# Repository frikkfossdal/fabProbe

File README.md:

# Fab Touchprobe 

## What is it

A fabrication friendly design of a 3-DOF touch probe. At the heart of the design is a circuit board that lights up leds on probe contact. Probe is designed to be attached on [Jake Read's hotplate system](https://clank.tools/build/hotplate/index.html). 

## How to use it

The probe acts as a digital switch. Connect it to your favorite machine controller and start probing. 

**NB! First batch of circuits has wrong labeling on connector input. Ground and input voltage is switched. Study circuit before connecting and chech yourself!**

## How to make it

The repo contains all the files that are necassary to print the parts and make the circuit. There are currently two circuit designs: one that is pcb mill friendly (not tested!) and one circuit design meant for fabrication houses. I'm using the latter. Some notes: 

- Originally the probe uses [threaded steel-balls]() and dowels to form the kinematic mount but this could be modified to only use screws and dowels for easier sourcing.
- I print the probe casing with two different filaments, one transparent for making the circuit leds visible and one solid gray. If you rather print the casing as one solid merge the two casing bodies. 
- If you want to use a different probing stylus change the "nut diameter" of the nut on the *probe base* (see fusion model) to fit your chosen diameter. 

## BOM

| **Part Name**       | **Description**                   | **Quantity** | **Link**                                                                                  |
|---------------------|-----------------------------------|--------------|-------------------------------------------------------------------------------------------|
| threaded steel ball | typically found in delta printers | 6            | [amazon](https://www.amazon.com/Bolsen-Threaded-Kossel-3D-Printer-Magnetic/dp/B07HQ72H1R) |
| steel dowels 5x10mm |                                   | 3            | [mcmaster](https://www.mcmaster.com/93600a511/)                                           |
| probe stylus m3x50  |                                   | 1            | [ebay](https://www.ebay.com/itm/132811711640)                                             |
| m4button x 8mm      |                                   | 6            | [mcmaster](https://www.mcmaster.com/93600a511/)                                           |
| m3button x 14mm     |                                   | 3            | [mcmaster](https://www.mcmaster.com/92095A168/)                                           |
| m3_locknut          |                                   | 3            | [mcmaster](https://www.mcmaster.com/90576A102/)                                           |

## Develop notes 

- After discussing with Jake we agreed that the design of the probe needs to be modified with some way of offsetting the centering of the probe. Revision will follow in near future. 
- [Here](https://www.youtube.com/watch?v=ZvX3S8Ky3Ok) is a video showing how centering is done on a renishaw probe.
- [Instructable](https://www.instructables.com/CNC-Touch-Probe-Calibration/) on calibrating probe using gcode.
- Spring force matters. I have to do more testing to find good sensitivity.

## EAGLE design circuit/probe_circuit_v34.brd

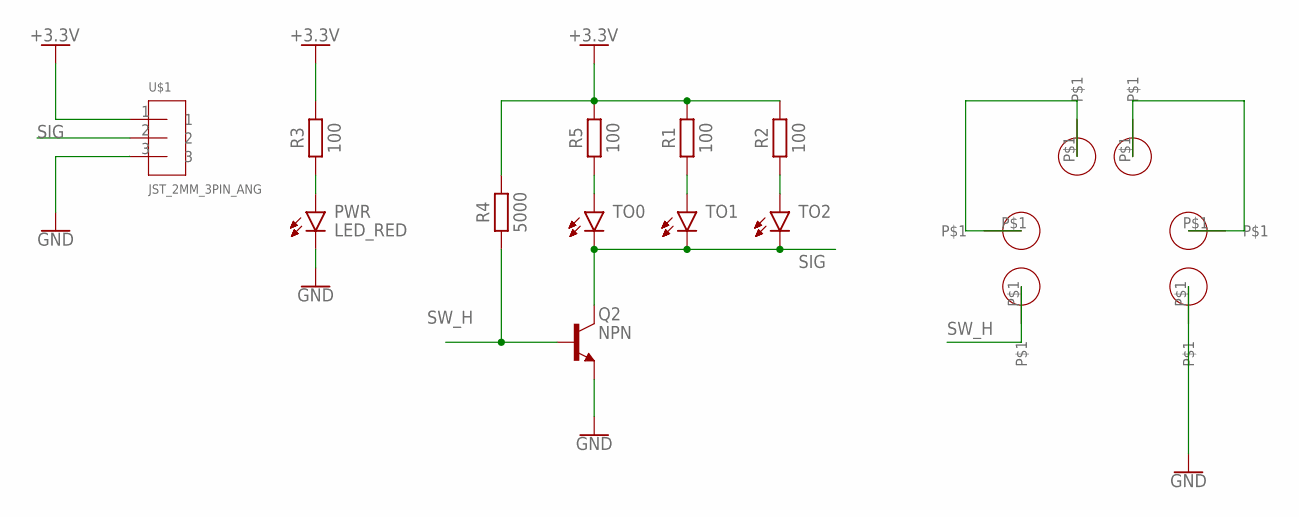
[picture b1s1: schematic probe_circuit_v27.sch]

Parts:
F0, F1, F2, F3, F4, F5: 4MM_HOLE
PWR: LED_RED; LEDC3216X75N_FLAT-R
Q2: NPN; SOT95P237X112-3N
R1, R2, R3, R5: 100; RESC1608X60
R4: 5000; RESC1608X60
TO0, TO1, TO2: LED_BLUE; LEDC3216X75N_FLAT-B
U$1: JST_2MM_3PIN_ANG

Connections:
+3.3V: R1.2, R2.2, R3.2, R4.2, R5.2, U$1.1
GND: F5.P$1, PWR.C, Q2.2 (E), U$1.3
unnamed: PWR.A, R3.1
unnamed: F1.P$1, F2.P$1
unnamed: R5.1, TO0.A
unnamed: F3.P$1, F4.P$1
unnamed: R1.1, TO1.A
unnamed: R2.1, TO2.A
SIG: Q2.3 (C), TO0.C, TO1.C, TO2.C, U$1.2
SW_H: F0.P$1, Q2.1 (B), R4.1

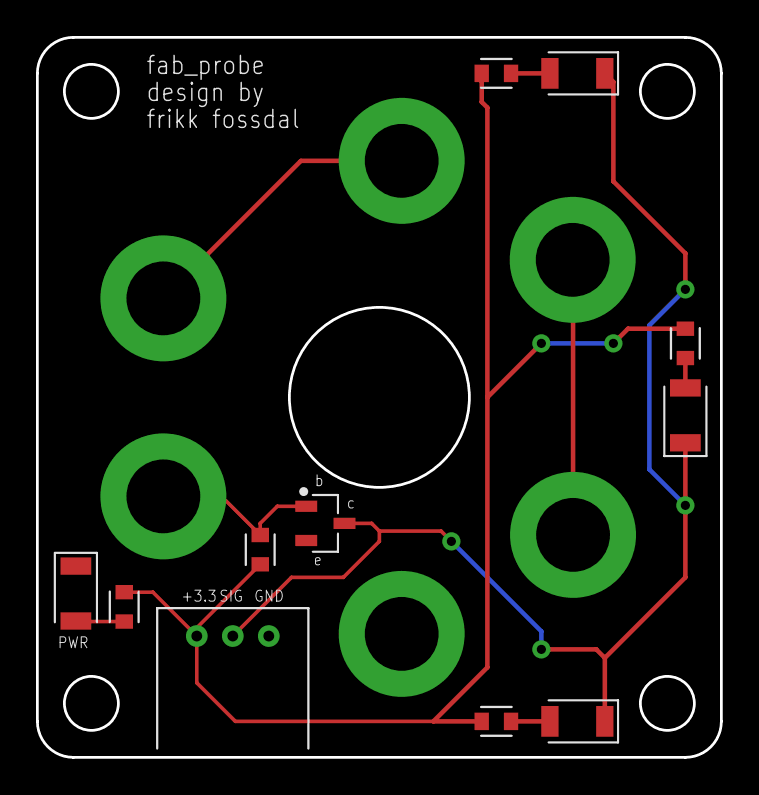
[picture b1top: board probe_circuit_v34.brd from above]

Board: 2 copper layers, 38.0 x 40.0 mm, 17 parts (0 on the bottom side), 10 nets.

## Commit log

2021-04-08 switching to mobile
2022-03-22 documentation first round of circuit
2022-03-22 added circuit files
    these are updated with transistor fix and text fix after debugging version 1
2022-05-04 new project folder
2022-05-18 updated files
2022-05-18 updated doc
2022-05-18 added meta-data
2022-08-17 added instructables gcode calib

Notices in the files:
parts and their libraries:
SparkFun-PowerSymbols: Licensing: Creative Commons ShareAlike 4.0 International - https://creativecommons.org/licenses/by-sa/4.0
